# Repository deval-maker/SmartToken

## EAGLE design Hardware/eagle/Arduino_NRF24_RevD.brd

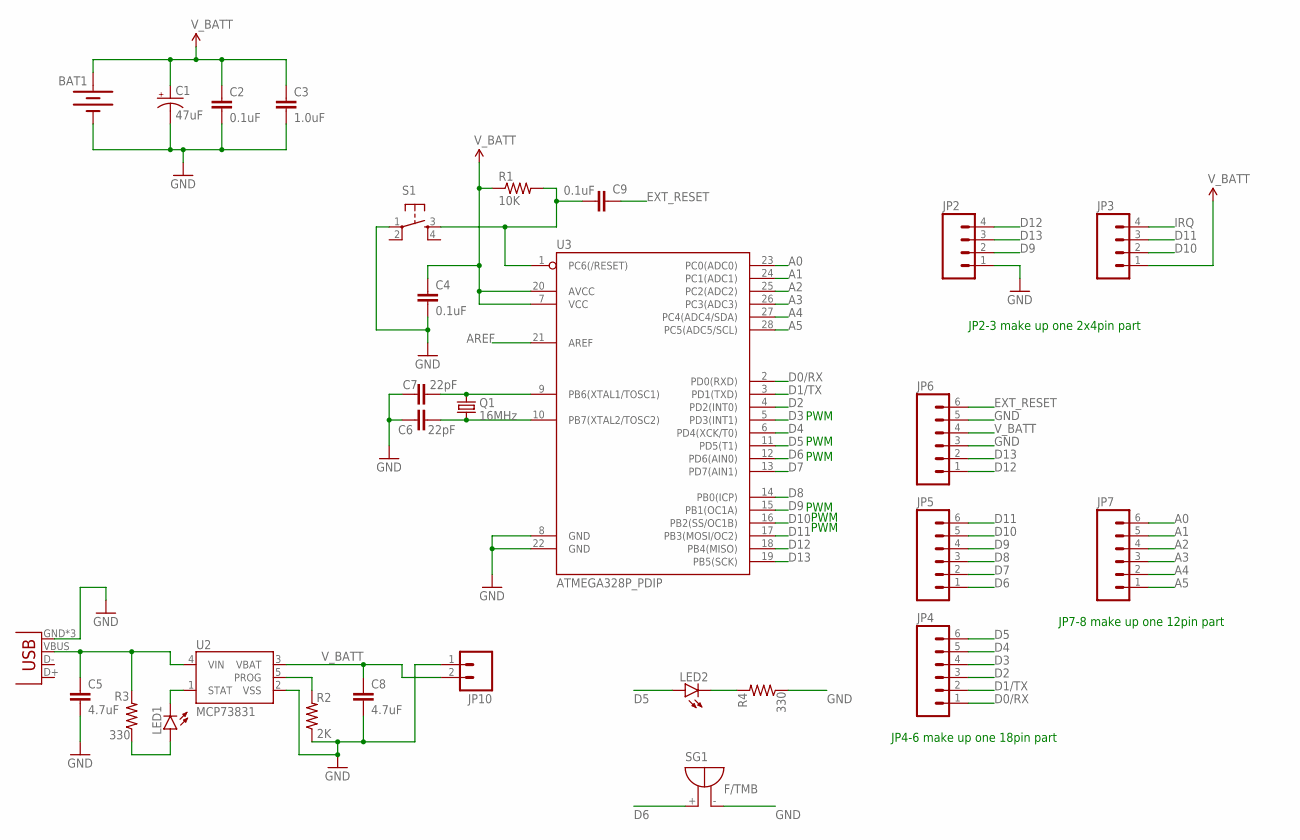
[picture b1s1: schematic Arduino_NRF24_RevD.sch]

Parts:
BAT1: 20mm coincell; BATTCON_20MM_4LEGS; MPN 1065
C1: 47uF; CPOL-RADIAL-100UF-25V; MPN MCTG470M1AB-0512P
C2, C4, C9: 0.1uF; CAP-PTH-SMALLEZ; MPN K104K15X7RF5TL2
C3: 1.0uF; CAP-PTH-SMALLEZ; MPN MCNP16V105M5X11
C5, C8: 4.7uF; CAP-PTH-SMALLEZ; MPN MCLV4R7M1HB-0513-RH
C6, C7: 22pF; CAP-PTH-SMALLEZ; MPN MCCC50V220JNPO
JP2, JP3: M04PTH; 1X04; MPN BIM-INT-Y1X-0.4M-RS 4.21T W/M
JP4, JP5, JP6, JP7: M06SIP; 1X06; MPN BI1.5-H6.5-Y1X-0.6M-RS4.21T
JP9: USB-MICROB; MPN USB3100-30-A
JP10: M02JST-PTH-2; JST-2-PTH; MPN 26-60-4020
LED1, LED2: LED5MM; MPN C503B-BCN-CV0Z0461
Q1: 16MHz; HC49U-V; MPN ABLSG-16.000MHZ-D-2-Y-T
R1: 10K; AXIAL-0.4; MPN MC0063W0603510K
R2: 2K; AXIAL-0.4; MPN 34-2K
R3, R4: 330; AXIAL-0.4; MPN MCF 0.5W 330R
S1: TAC_SWITCHSMD; TACTILE_SWITCH_SMD; MPN 1571218-6
SG1: F/TMB; MPN MCKPI-G2913L-3973
U2: MCP73831; SOT23-5; MPN MCP73831T-2ACI/OT
U3: ATMEGA328P_PDIP; DIL28-3; MPN ATMEGA328P-PU

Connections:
A0: JP7.6, U3.23 (PC0(ADC0))
A1: JP7.5, U3.24 (PC1(ADC1))
A2: JP7.4, U3.25 (PC2(ADC2))
A3: JP7.3, U3.26 (PC3(ADC3))
A4: JP7.2, U3.27 (PC4(ADC4/SDA))
A5: JP7.1, U3.28 (PC5(ADC5/SCL))
AREF: U3.21 (AREF)
D0/RX: JP4.1, U3.2 (PD0(RXD))
D1/TX: JP4.2, U3.3 (PD1(TXD))
D2: JP4.3, U3.4 (PD2(INT0))
D3: JP4.4, U3.5 (PD3(INT1))
D4: JP4.5, U3.6 (PD4(XCK/T0))
D5: JP4.6, LED2.A, U3.11 (PD5(T1))
D6: JP5.1, SG1.+, U3.12 (PD6(AIN0))
D7: JP5.2, U3.13 (PD7(AIN1))
D8: JP5.3, U3.14 (PB0(ICP))
D9: JP2.2, JP5.4, U3.15 (PB1(OC1A))
D10: JP3.2, JP5.5, U3.16 (PB2(SS/OC1B))
D11: JP3.3, JP5.6, U3.17 (PB3(MOSI/OC2))
D12: JP2.4, JP6.1, U3.18 (PB4(MISO))
D13: JP2.3, JP6.2, U3.19 (PB5(SCK))
EXT_RESET: C9.1, JP6.6
GND: BAT1.2 (-), C1.2 (-), C2.2, C3.2, C4.2, C5.2, C6.1, C7.2, C8.2, JP2.1, JP6.3, JP6.5, JP9.GND, JP9.MT1 (GND), JP9.MT2 (GND), JP10.1, R2.P$1 (1), R4.P$1 (1), S1.1, SG1.-, U2.2 (VSS), U3.8 (GND), U3.22 (GND)
IRQ: JP3.4
unnamed: C7.1, Q1.1, U3.9 (PB6(XTAL1/TOSC1))
unnamed: C6.2, Q1.2, U3.10 (PB7(XTAL2/TOSC2))
unnamed: LED1.K (C), U2.1 (STAT)
unnamed: LED1.A, R3.P$1 (1)
unnamed: C5.1, JP9.VBUS, R3.P$2 (2), U2.4 (VIN)
unnamed: LED2.K (C), R4.P$2 (2)
unnamed: R2.P$2 (2), U2.5 (PROG)
RESET: C9.2, R1.P$2 (2), S1.3, U3.1 (PC6(/RESET))
V_BATT: BAT1.1 (+), C1.1 (+), C2.1, C3.1, C4.1, C8.1, JP3.1, JP6.4, JP10.2, R1.P$1 (1), U2.3 (VBAT), U3.7 (VCC), U3.20 (AVCC)

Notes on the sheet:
JP4-6 make up one 18pin part
JP7-8 make up one 12pin part
JP2-3 make up one 2x4pin part
PWM

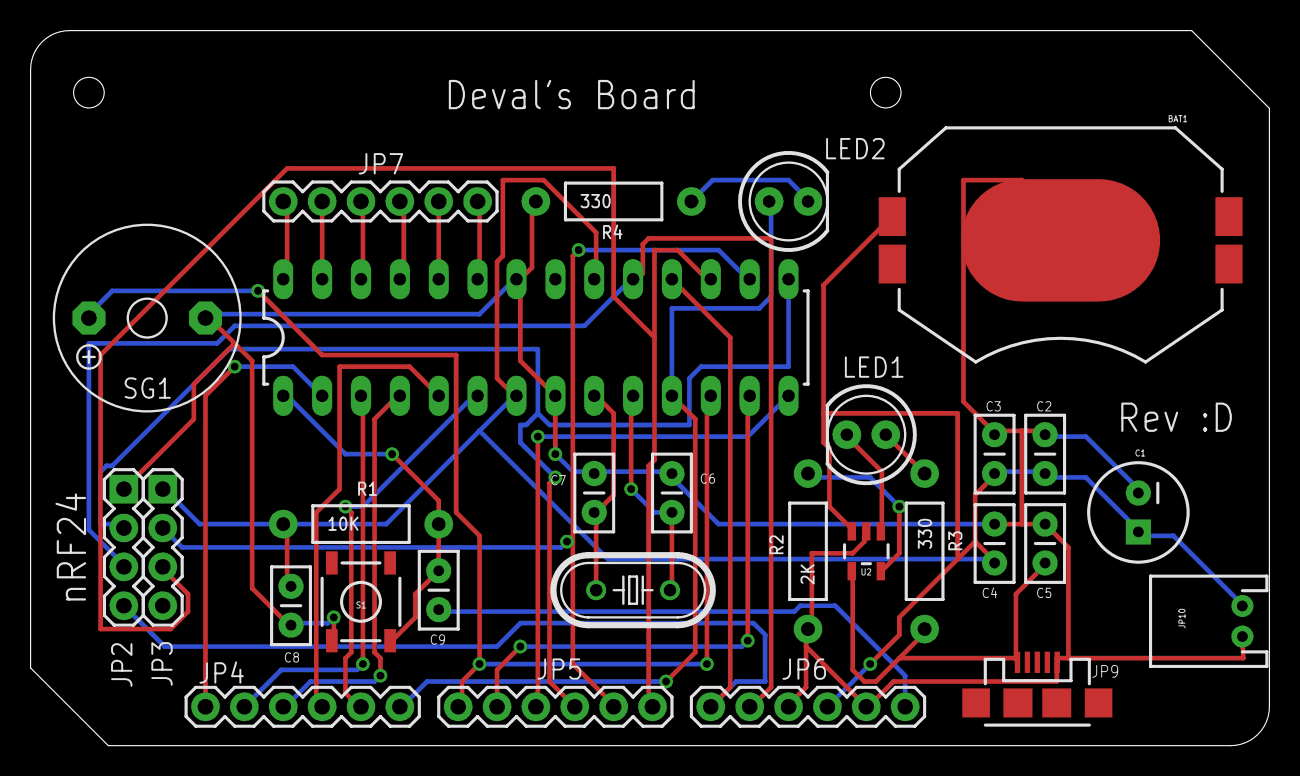
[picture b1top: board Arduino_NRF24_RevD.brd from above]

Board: 2 copper layers, 81.0 x 46.7 mm, 29 parts (0 on the bottom side), 31 nets.

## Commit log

2015-11-22 Initial commit with hardware files ready for production.

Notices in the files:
parts and their libraries:
SparkFun-Electromechanical: Licensing: CC v3.0 Share-Alike You are welcome to use this library for commercial purposes.
SparkFun-LED: Licensing: Creative Commons ShareAlike 4.0 International - https://creativecommons.org/licenses/by-sa/4.0
